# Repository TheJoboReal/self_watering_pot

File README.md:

### Intro
This project is for an elective self study course on SDU and concerns a very low powered self watering plant pot, using a pico pi. The theoretical battery life based on the component datasheets is approx 3 months on an 1800mAh lithium battery.

### Code
All code is written in C and uses a simple run to complete scheduler.

It can be compiled with:

```bash
mkdir build 
cd build 
cmake ..
cd ..
```

and build with:

```bash
cmake --build build
```

### PCB
PCB is designed in FreeCAD and meant to house all the components used in the project. It is recommended to use sockets for the pin modules to enable quick swap of possible damaged components(Lesson learned the hard way..).

### TODO
* Implement SD card logging.
* Replace burnt Eink and make UI interactable with encoder.
* Add soldering pad for an esp32 to allow choice between pico pi and esp.

### Acknowledgements 
CAD design is derived from the CAD work of Martin [here](https://www.thingiverse.com/thing:4921885).

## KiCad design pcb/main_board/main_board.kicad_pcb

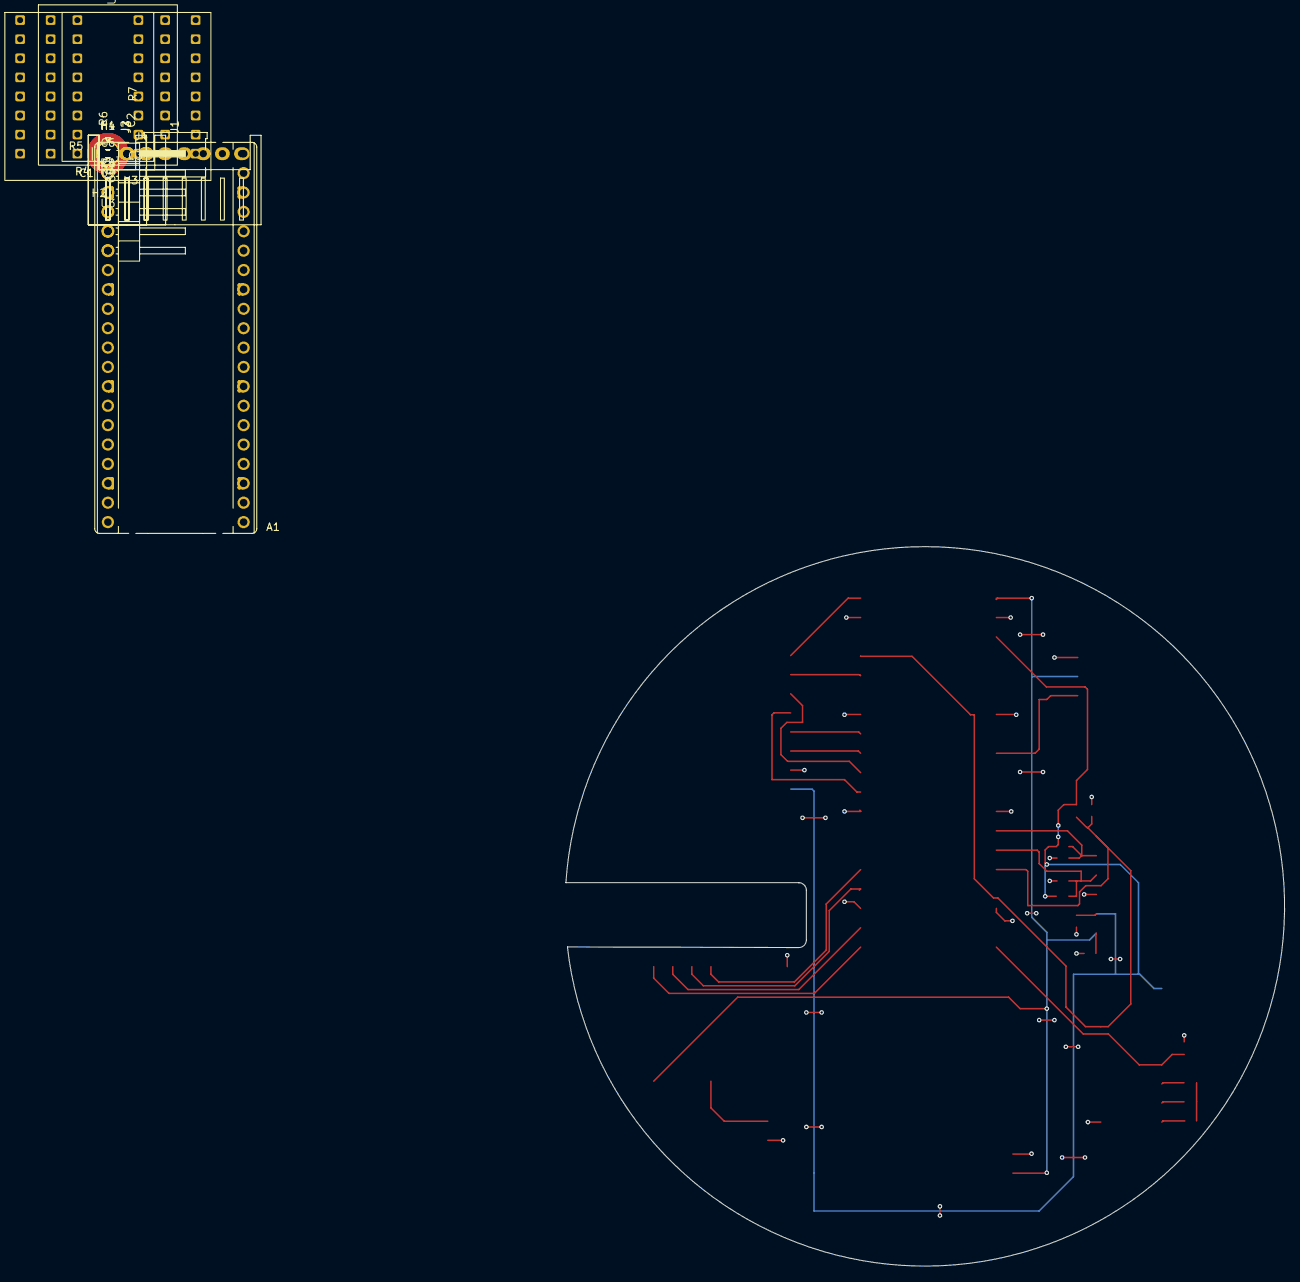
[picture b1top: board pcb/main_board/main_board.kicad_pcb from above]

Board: 2 copper layers, 94.1 x 94.2 mm, 24 parts (0 on the bottom side), 23 nets.

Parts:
A1: RaspberryPi_Pico; RaspberryPi_Pico_Common_THT
C1: 1muF; C_0603_1608Metric
C2, C3, C4, C5, C6: 47pF; C_0603_1608Metric
H1, H2, H3, H4: MountingHole; MountingHole_2.7mm_Pad_TopBottom
J1: Conn_01x08; JST_XH_S8B-XH-A_1x08_P2.50mm_Horizontal
J2: Conn_01x02_Socket; JST_XH_S2B-XH-A_1x02_P2.50mm_Horizontal
J3: Conn_01x03_Socket; JST_XH_S3B-XH-A_1x03_P2.50mm_Horizontal
J4: Conn_01x06; PinHeader_1x06_P2.54mm_Horizontal
R3: 12M; R_0603_1608Metric
R4: 1.2M; R_0603_1608Metric
R5, R6, R7, R8: 100k; R_0603_1608Metric
U1: CD74HC4060E
U2: TB6612FNG
U3: wemos_battery_shield; Untitled

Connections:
+3.3V: A1.37 (3V3_EN), C5.1, J1.8, J4.5, R6.1, R7.1, R8.1, U1.16 (VCC)
+5V: A1.39 (VSYS), C6.1, J3.2, J4.6, U2.8 (VM), U3.1 (5V)
/EI_BUSY: A1.2 (GPIO1), J1.1
/EI_CS: A1.12 (GPIO9), J1.4
/EI_DC: A1.11 (GPIO8), J1.3
/EI_MOSI: A1.10 (GPIO7), J1.6
/EI_RST: A1.6 (GPIO4), J1.2
/EI_SCLK: A1.9 (GPIO6), J1.5
/ENC_A: A1.26 (GPIO20), C4.1, J4.3, R8.2
/ENC_B: A1.27 (GPIO21), C3.1, J4.2, R7.2
/ENC_BUT: A1.5 (GPIO3), A1.25 (GPIO19), C2.1, J4.1, R6.2, U1.3 (Q14)
/MOIST_AOUT: A1.31 (GPIO26_ADC0), J3.1
/MTR_AIN1: A1.17 (GPIO13), U2.14 (AIN1)
/MTR_AIN2: A1.19 (GPIO14), U2.15 (AIN2)
/MTR_AO1: J2.1, U2.5 (AO1)
/MTR_PWM_A: A1.20 (GPIO15), U2.16 (PWMA)
/MTR_STBY: A1.16 (GPIO12), U2.13 (STBY)
/SLEEP_RST: A1.21 (GPIO16), R5.2, U1.12 (MR)
GND: A1.3 (GND), A1.8 (GND), A1.13 (GND), A1.18 (GND), A1.23 (GND), A1.28 (GND), A1.33 (AGND), A1.38 (GND), C2.2, C3.2, C4.2, C5.2, C6.2, J1.7, J2.2, J3.3, J4.4, R5.1, U1.8 (GND), U2.9 (GND), U3.2 (GND)
unnamed: C1.1, U1.9 (O)
unnamed: C1.2, R3.1, R4.1
unnamed: R4.2, U1.10 (O)
unnamed: R3.2, U1.11 (I)

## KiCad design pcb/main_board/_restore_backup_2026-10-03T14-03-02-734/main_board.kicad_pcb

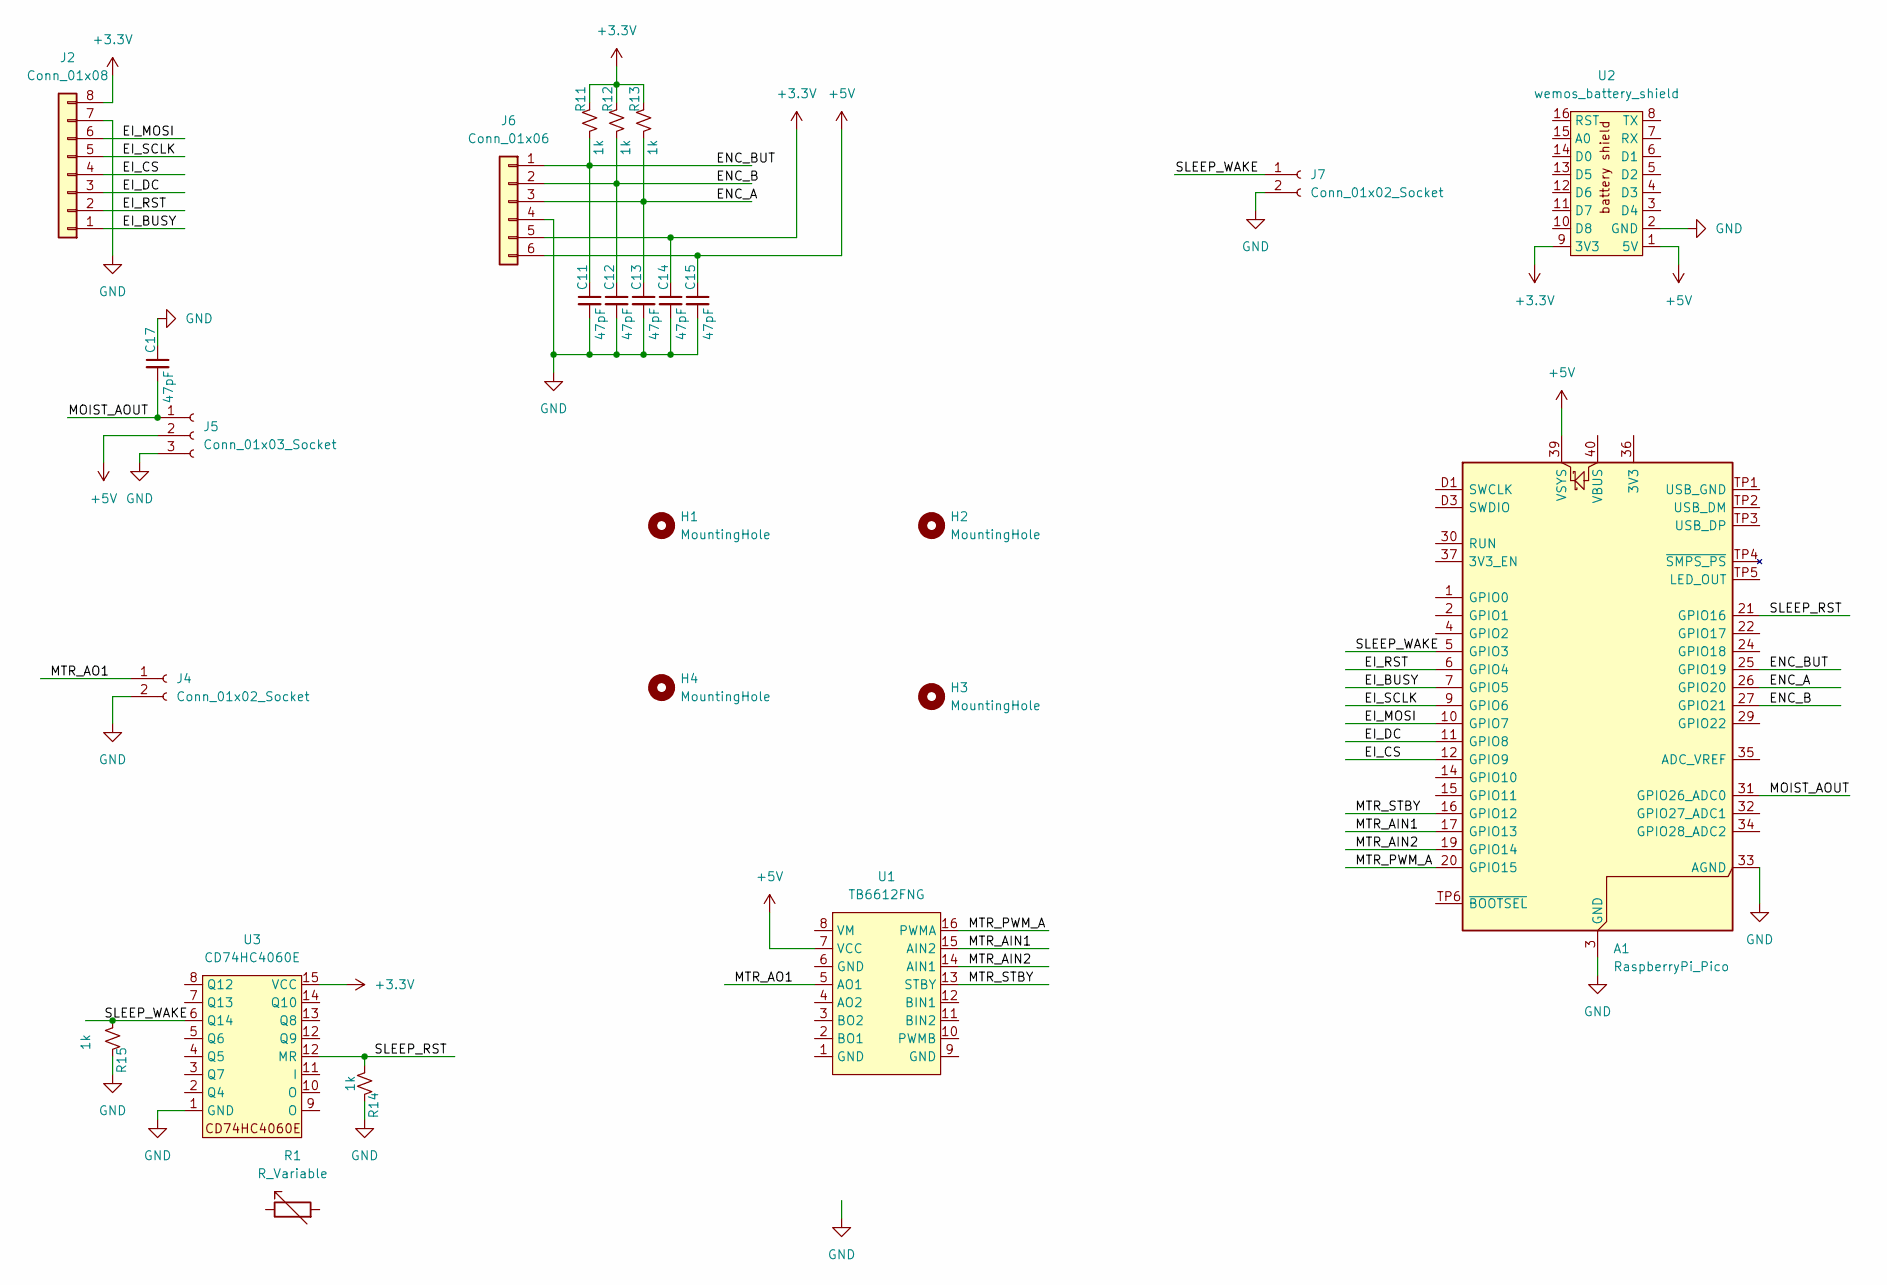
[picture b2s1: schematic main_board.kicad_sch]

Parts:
A1: RaspberryPi_Pico; RaspberryPi_Pico_Common_THT
C11, C12, C13, C14, C15, C17: 47pF; C_0603_1608Metric
H1, H2, H3, H4: MountingHole; MountingHole_2.5mm_Pad_TopBottom
J2: Conn_01x08; JST_XH_S8B-XH-A_1x08_P2.50mm_Horizontal
J4, J7: Conn_01x02_Socket; JST_XH_S2B-XH-A_1x02_P2.50mm_Horizontal
J5: Conn_01x03_Socket; JST_XH_S3B-XH-A_1x03_P2.50mm_Horizontal
J6: Conn_01x06; PinHeader_1x06_P2.54mm_Horizontal
R1: R_Variable
R11, R12, R13, R14, R15: 1k; R_0603_1608Metric
U1: TB6612FNG
U2: wemos_battery_shield; Untitled
U3: CD74HC4060E

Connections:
+3.3V: C14.1, J2.8, J6.5, R11.1, R12.1, R13.1, U2.9 (3V3), U3.15 (VCC)
+5V: A1.39 (VSYS), C15.1, J5.2, J6.6, U1.7 (VCC), U2.1 (5V)
/EI_BUSY: A1.7 (GPIO5), J2.1
/EI_CS: A1.12 (GPIO9), J2.4
/EI_DC: A1.11 (GPIO8), J2.3
/EI_MOSI: A1.10 (GPIO7), J2.6
/EI_RST: A1.6 (GPIO4), J2.2
/EI_SCLK: A1.9 (GPIO6), J2.5
/ENC_A: A1.26 (GPIO20), C13.1, J6.3, R13.2
/ENC_B: A1.27 (GPIO21), C12.1, J6.2, R12.2
/ENC_BUT: A1.25 (GPIO19), C11.1, J6.1, R11.2
/MOIST_AOUT: A1.31 (GPIO26_ADC0), C17.2, J5.1
/MTR_AIN1: A1.17 (GPIO13), U1.15 (AIN2)
/MTR_AIN2: A1.19 (GPIO14), U1.14 (AIN1)
/MTR_AO1: J4.1, U1.5 (AO1)
/MTR_PWM_A: A1.20 (GPIO15), U1.16 (PWMA)
/MTR_STBY: A1.16 (GPIO12), U1.13 (STBY)
/SLEEP_RST: A1.21 (GPIO16), R14.2, U3.12 (MR)
/SLEEP_WAKE: A1.5 (GPIO3), J7.1, R15.2, U3.6 (Q14)
GND: A1.3 (GND), A1.8 (GND), A1.13 (GND), A1.18 (GND), A1.23 (GND), A1.28 (GND), A1.33 (AGND), A1.38 (GND), A1.D2 (GND), C11.2, C12.2, C13.2, C14.2, C15.2, C17.1, J2.7, J4.2, J5.3, J6.4, J7.2, R14.1, R15.1, U2.2 (GND), U3.1 (GND)

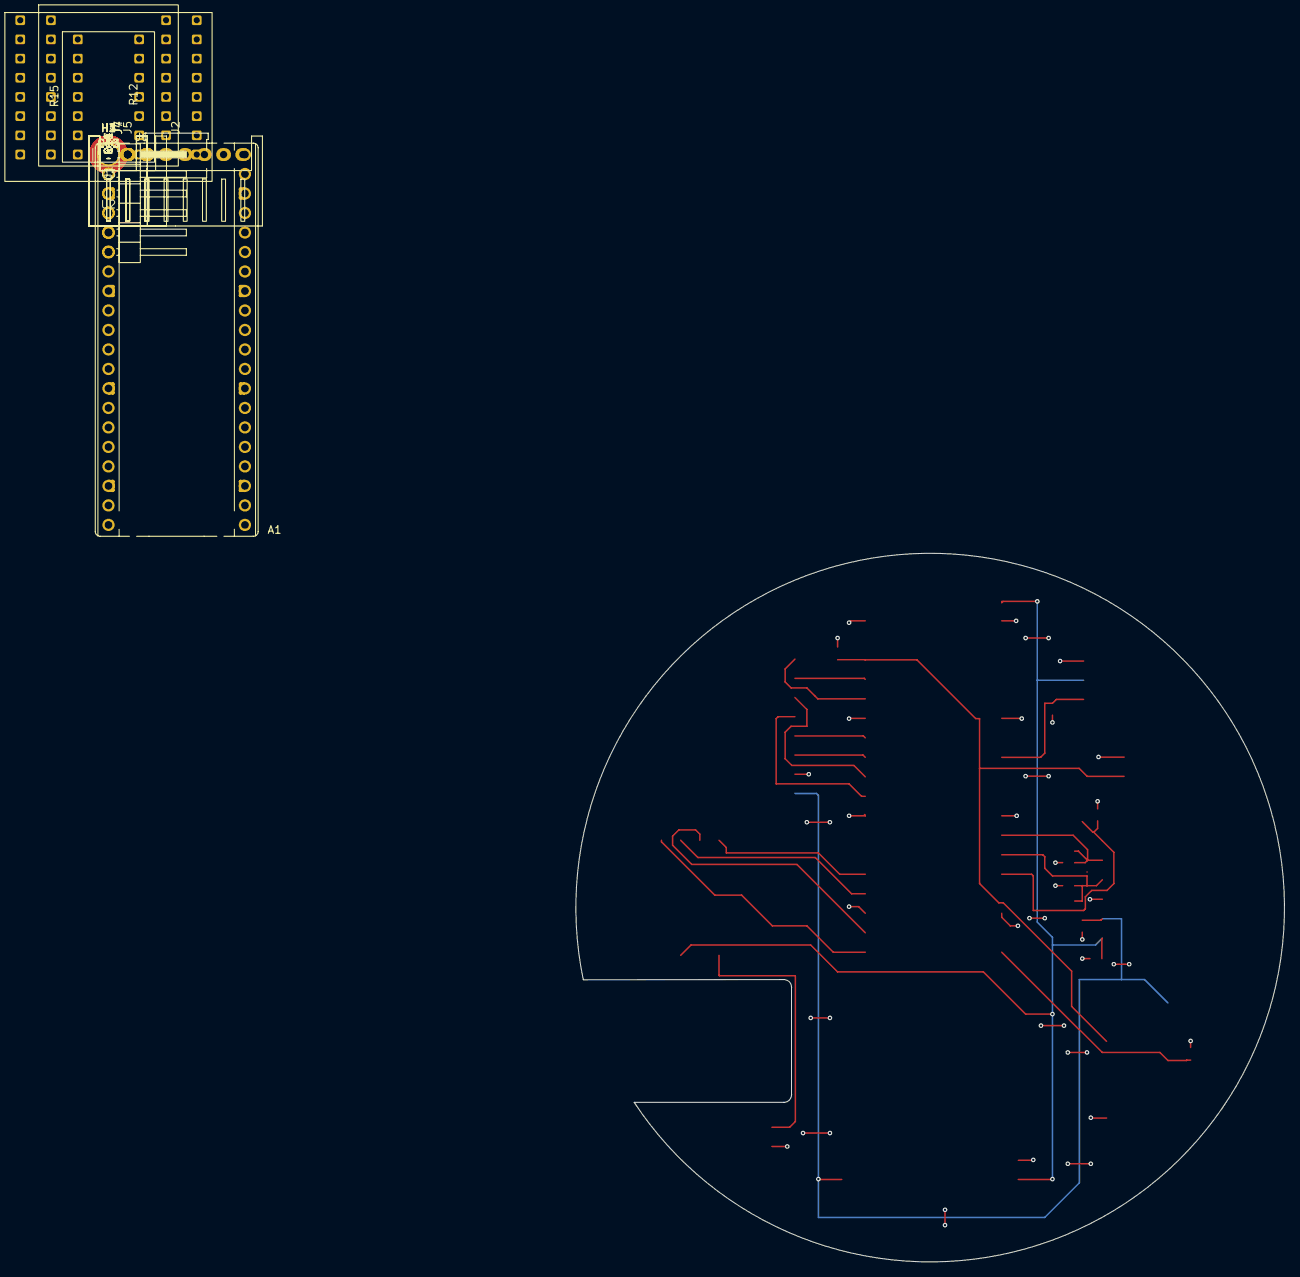
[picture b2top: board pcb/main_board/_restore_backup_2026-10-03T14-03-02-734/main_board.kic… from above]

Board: 2 copper layers, 92.3 x 92.3 mm, 24 parts (0 on the bottom side), 20 nets.

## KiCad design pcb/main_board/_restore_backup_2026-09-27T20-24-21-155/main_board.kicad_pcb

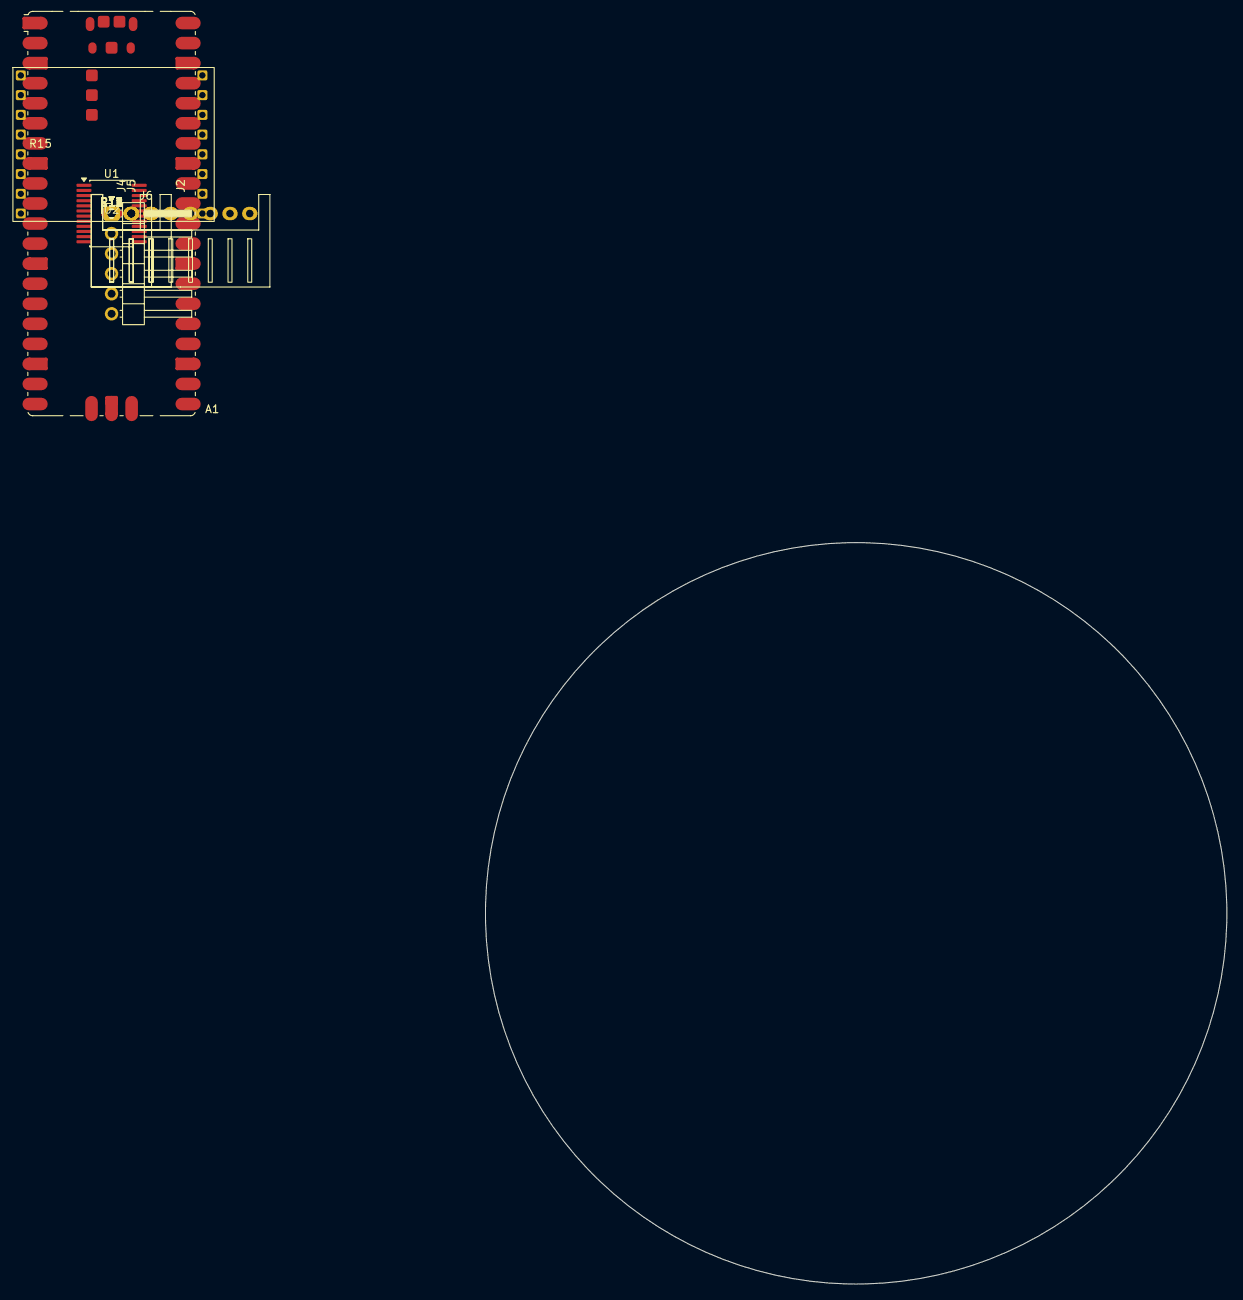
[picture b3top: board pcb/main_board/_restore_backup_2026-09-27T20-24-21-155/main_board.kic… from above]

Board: 2 copper layers, 93.9 x 93.9 mm, 17 parts (0 on the bottom side), 23 nets, no tracks yet.

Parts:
A1: RaspberryPi_Pico; RaspberryPi_Pico_SMD
C11, C12, C13, C14, C15: 470pF; C_0603_1608Metric
J2: Conn_01x08; JST_XH_S8B-XH-A_1x08_P2.50mm_Horizontal
J4: Conn_01x02_Socket; JST_XH_S2B-XH-A_1x02_P2.50mm_Horizontal
J5: Conn_01x03_Socket; JST_XH_S3B-XH-A_1x03_P2.50mm_Horizontal
J6: Conn_01x06; PinHeader_1x06_P2.54mm_Horizontal
R11, R12, R13, R14, R15: 1k; R_0603_1608Metric
U1: TB6612FNG; SSOP-24_5.3x8.2mm_P0.65mm
U2: Wemos_battery_shield

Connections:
+3.3V: C14.1, J2.8, J6.5, R11.1, R12.1, R13.1
+5V: A1.39 (VSYS), C15.1, J5.2, J6.6, U1.20 (VCC)
/EI_CS: A1.12 (GPIO9), J2.4
/EI_DC: A1.11 (GPIO8), J2.3
/EI_MOSI: A1.10 (GPIO7), J2.6
/EI_RST: A1.6 (GPIO4), J2.2
/EI_SCLK: A1.9 (GPIO6), J2.5
/ENC_A: C13.1, J6.3, R13.2
/ENC_B: C12.1, J6.2, R12.2
/ENC_BUT: C11.1, J6.1, R11.2
/MOIST_AOUT: A1.31 (GPIO26_ADC0), J5.1
/MTR_AIN1: A1.17 (GPIO13), U1.21 (AIN1)
/MTR_AIN2: A1.19 (GPIO14), U1.22 (AIN2)
/MTR_PWM_A: A1.20 (GPIO15), U1.23 (PWMA)
/MTR_STBY: A1.16 (GPIO12), U1.19 (STBY)
/SLEEP_WAKE: A1.7 (GPIO5), R15.2
GND: A1.3 (GND), A1.8 (GND), A1.13 (GND), A1.18 (GND), A1.23 (GND), A1.28 (GND), A1.33 (AGND), A1.38 (GND), A1.D2 (GND), C11.2, C12.2, C13.2, C14.2, C15.2, J2.7, J4.2, J5.3, J6.4, R14.1, R15.1, U1.18 (GND)
unnamed: U1.1 (AO1), U1.2 (AO1)
unnamed: U1.5 (AO2), U1.6 (AO2)
unnamed: U1.11 (BO1), U1.12 (BO1)
unnamed: U1.7 (BO2), U1.8 (BO2)
unnamed: U1.3 (PGND1), U1.4 (PGND1)
unnamed: U1.9 (PGND2), U1.10 (PGND2)

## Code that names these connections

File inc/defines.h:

// Pins
#define ADC_PIN 26

// Dormant sleep mode
#define LOW_POWER_WAKE_GPIO 3
#define CLOCK_RST 16

// Pump
#define MOTOR_PWM_PIN 15
#define MOTOR_AIN2 14
#define MOTOR_AIN1 13
#define MOTOR_STBY 12

// Encoder
#define ENC_BUT 19
#define ENC_A 20
#define ENC_B 21

// EINK
#define EI_BUSY 1 
#define EI_RST 4
#define EI_SCLK 6
#define EI_MOSI 7
#define EI_DC 8
#define EI_CS 9

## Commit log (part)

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2026-03-31 init
2026-04-12 added esp project
2026-04-13 setup oled display
2026-05-08 added flake
2026-06-01 updated flake stuff
